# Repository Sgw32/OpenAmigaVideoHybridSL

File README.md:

# OpenAmigaVideoHybrid

!!! This version is the same, but is modified for cheaper manufacturing, only Single Sided component placement. 

OpenAmigaVideoHybrid is an Open Hardware implementation of the Video Hybrid integrated circuit used in some Commodore Amiga computers (Commodore Part No. 390229-0x).

### Summary
The *Video Hybrid*, also known as *VIDIOT*, is a hybrid integrated circuit acting as a Digital-to-Analog Converter (DAC), which converts the digital 4-bit per color video signal of the Amiga into standard (analog) signals suitable to drive a monitor or TV.

It is used in Amiga models A500, A500+, A1000, A2000 and A3000. The Amiga 3000 actually uses two Hybrids: one for the 15kHz video output from Denise and one for the 31kHz video output from Amber. Two Hybrids are also used in the [GBA1000 A1000 Clone](https://www.amigawiki.org/doku.php?id=de:models:gb_a1000).

It is also used in some add-on cards, such as the [Commodore A2320 Deinterlacer](https://amiga.resource.cx/exp/a2320).

The Video Hybrid is a reliable component that usually "just works", but if it gets damaged there is no way of repairing it, the only option is to replace it.

### Architecture
The Video Hybrid has 5 sections, one for each of the red, green and blue colors, one for the synchronization signal and one for a composite monochrome signal.

The red, green and blue sections are identical: first, the digital signals are mixed together using the typical *binary-weighted resistors* DAC configuration. After that, the level of the resulting signal is amplified through an NPN transistor. At the output, the signal is terminated at 75 ohms, as is typical for video signals.

The composite signal is generated in a similar way. The only significant differences are that the weighting resistors have different values and that the amplifier has two stages (NPN + PNP), in order to achieve a higher gain.

The synchronization signal is digital by nature, thus it needs no conversion, only some amplification.

### Components
It should now be clear that the Video Hybrid is not much more than a bunch of resistors and transistors, plus a few capacitors.

The original Video Hybrid uses a lot of resistance values which are rather odd by today's standards. While resistors with said values can still be found, they are becoming increasingly rarer and rather expensive.

Besides that, while the basic circuit has always remained the same, Commodore has used different values for some resistors in different revisions of the Video Hybrid. In particular, revision 3 uses higher resistance values in the synchronization signal section. Presumably, this was done to suppress crosstalk among the RGB channels (especially at 31kHz).

What this all means is that newer designs should use different values that are cheap and easy to find, while maintaining functionality and performance.

The tables below lists the component values originally used by Commodore, along with some alternative values readily available in the E24 series, which is common and cheap today. Another column shows the values I actually use.

|Resistors                                     |390229-01/02|390229-03|E24   |Sukko's     |Manufacturer Part Number (MPN)               |
|----------------------------------------------|------------|---------|------|------------|---------------------------------------------|
|R1, R9, R17, R25\*\*                          |1k          |1k       |1k    |1k          |CRG0805F1K0                                  |
|R2, R10, R18                                  |2k          |2k       |2k    |2k          |RMC1/10K202FTP                               |
|R3\*, R11\*, R19\*                            |4k          |4k       |3.9k  |8.2k\|\|8.2k|4.02k = CRCW08054K02FKEA, 3.9k = CRG0805F3K9 |
|R4\*, R12\*, R20\*                            |8k          |8k       |8.2k  |8.2k        |8.06k = CRCW08058K06FKEA, 8.2k = CRG0805F8K2 |
|R5, R13, R21                                  |470         |470      |470   |470         |CRG0805F470R                                 |
|R6, R14, R22                                  |390         |390      |390   |390         |CRG0805F390R                                 |
|R7, R8, R15, R16, R23, R24, R29\*\*, R39\*\*\*|75          |75       |75    |75          |ERJ6RED75R0V                                 |
|R26\*\*                                       |220         |220      |220   |220         |CRG0805F220R                                 |
|R27\*\*                                       |27k         |27k      |27k   |22k         |27k = CRG0805F27K                            |
|R28\*\*                                       |150         |150      |150   |220         |150 = CRG0805F150R                           |
|R30\*\*\*                                     |18k         |90.9k    |91k   |100k        |                                             |
|R31\*\*\*                                     |7.5k        |37.4k    |62k   |68k         |68k = CRG0805F68K                            |
|R32\*\*\*                                     |2.7k        |13.3k    |22k   |22k         |22k = RMC1/10K223FTP                         |
|R33\*\*\*                                     |1.2k        |6.04k    |10k   |22k\|\|22k  |                                             |
|R34\*\*\*                                     |7.5k        |37.4k    |62k   |68k         |                                             |
|R35\*\*\*                                     |3.9k        |19.6k    |20k   |22k         |                                             |
|R36\*\*\*                                     |120         |270      |220   |220         |                                             |
|R37\*\*\*, R38\*\*\*                          |36          |36       |36    |75\|\|75    |                                             |
|**Different Parts Count**                     |**17**      |**17**   |**16**|**10**      |                                             |

|Other Components                    |Value/MPN|
|------------------------------------|---------|
|C1, C2, C3, C4\*\*, C5\*\*\*        |100nF    |
|Q1, Q2, Q3, Q4\*\*, Q5\*\*\*        |MMBT3904 |
|Q6\*\*\*                            |MMBT3906 |

Notes:
- To achieve the highest video quality, it is strongly recommended to **use resistors with 1% tolerance** (or less) everywhere.
- *In theory*, components marked with a single asterisk* are crucial for a precise and coherent conversion of color data from digital to analog, therefore it should be recommended to stay as close as possible to the original values used by Commodore, encouraging the usage of 4.02k and 8.06k resistors (properly from the E96 series). *In practice*, my eye can't see any apparent differences when using the indicated values from the E24 series.
- Components marked with two asterisks\*\* are only used by the circuit that amplifies the synchronization signal. Normally, Amigas bring to the video connector only the raw, unamplified signal, making this circuit, and thus these components, totally useless. This is the case, for instance, on A500 Rev.5 boards, where the signal is unrouted. On A500 Rev.8A boards, the amplified and unamplified signals are brought to a jumper pad (JP11), which by default connects the unamplified signal. I'm currently not sure on what other mainboard revisions and other Amiga models do, but there's a good chance that you can get away without mounting these components at all.
- Components marked with three asterisks\*\*\* are only used by the circuit that generates the composite video signal. Since most of the original resistor values are uncommon, and since I don't think anybody really uses the composite output at all, I would just recommend not to mount these parts. If you really care for the (monochrome!) composite output, I wouldn't bother hunting down the correct parts and would just use the approximate values from the E24 series: they might produce a signal that is out-of-standard and that might blow your TV (I take no responsibility, use at your own risk!), but my tests show that they yield a decent image that can still be used for whatever a monochrome output can be useful for. Finally, note that all of these components (and only them!) have been grouped on the back side of the board for quick identification.
- Values listed in the *Sukko's* column are those that I actually use, in order to cut component costs and the number of different components. The \|\| symbol means "parallel", i.e.: just solder two resistors one over the other. These values work fine with my A500 and my TV and yield results that are satifactory for me, but they might produce a signal that is out-of-standard and that might blow your TV. Again, I take no responsibility, use at your own risk!
- The last column lists the MPN (Manufacturer Part Number) for some reasonably-priced components that I personally tested. With that number, you will be able to buy that exact model of component I used in any shop that's selling electronic components.

### Installation
Currently, OpenAmigaVideoHybrid has only been tested on the A500. On this model, you can mount it in vertical as the original Video Hybrid by using 90-degree pin headers, but I recommend a different approach:
- Remove your original Video Hybrid, taking care not to lift any traces.
- Install a row of [female *machined header pins*](https://raw.githubusercontent.com/SukkoPera/OpenAmigaVideoHybrid/master/doc/round_pin_headers_female.jpg): these will allow you to install again an original Commodore Video Hybrid, should you want to, and [it will fit snugly](https://raw.githubusercontent.com/SukkoPera/OpenAmigaVideoHybrid/master/doc/original_socketed.jpg).
- Solder a row of [male *machined header pins*](https://raw.githubusercontent.com/SukkoPera/OpenAmigaVideoHybrid/master/doc/round_pin_headers_male.jpg) to your OpenAmigaVideoHybrid: now [it will also fit just as snugly](https://raw.githubusercontent.com/SukkoPera/OpenAmigaVideoHybrid/master/doc/oavh_installed.jpg) and rest just above the output video buffer chips, without touching them and ensuring sufficient heat dissipation.

### License
OpenAmigaVideoHybrid is Open Hardware. If you make any modifications to the board, please contribute them back.

### Disclaimer
OpenAmigaVideoHybrid is provided to you ‘as is’ and without any express or implied warranties whatsoever with respect to its functionality, operability or use, including, without limitation, any implied warranties of merchantability, fitness for a particular purpose or infringement. We expressly disclaim any liability whatsoever for any direct, indirect, consequential, incidental or special damages, including, without limitation, lost revenues, lost profits, losses resulting from business interruption or loss of data, regardless of the form of action or legal theory under which the liability may be asserted, even if advised of the possibility or likelihood of such damages.

### Support the Project
Since the project is open you are free to get the PCBs made by your preferred manufacturer, however in case you want to support the development, you can order them from PCBWay through this link:

You get cheap, professionally-made and good quality PCBs, I get some credit that will help with this and [other projects](https://www.pcbway.com/project/member/shareproject/?bmbid=41100). You won't even have to worry about the various PCB options, it's all pre-configured for you!

Also, if you still have to register to that site, [you can use this link](https://www.pcbway.com/setinvite.aspx?inviteid=41100) to get some bonus initial credit (and yield me some more).

Again, if you want to use another manufacturer, feel free to, don't feel obligated :).

### Get Support
If you need help or have questions, you can join [the official Telegram group](https://t.me/joinchat/HUHdWBC9J9JnYIrvTYfZmg).

### Thanks
- The PCB layout was initially inspired by [kipper2k's Video Hybrid Replacement](http://eab.abime.net/showthread.php?t=68311).
- This page contains a lot of content translated from [amigawiki](http://www.amigawiki.de/doku.php?id=de:parts:vidiot).
- [A good tutorial on DAC architectures](http://www.circuitstoday.com/digital-to-analog-converters-da) helped me to get a better understanding of DACs.
- [This](http://logwell.com/tech/components/resistor_values.html) helped me understand the rationale behind the actual resistor values available on the market.

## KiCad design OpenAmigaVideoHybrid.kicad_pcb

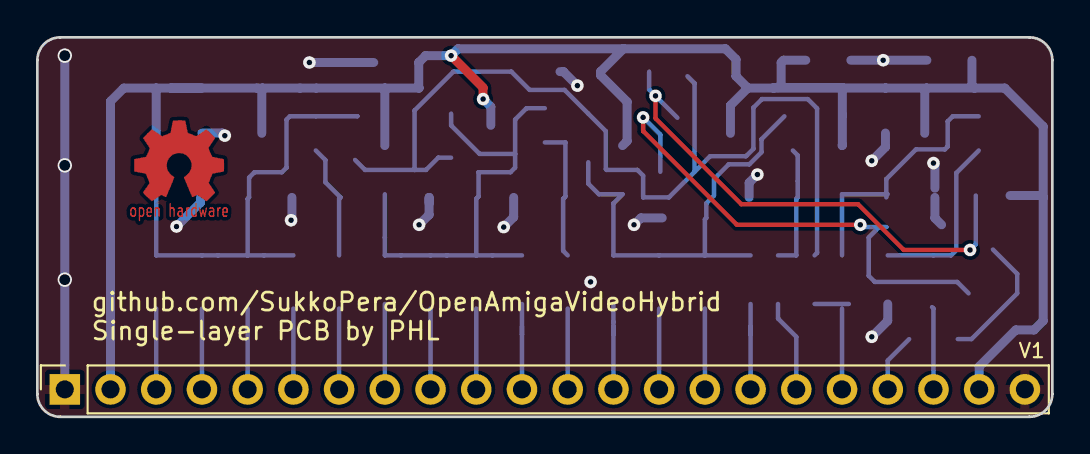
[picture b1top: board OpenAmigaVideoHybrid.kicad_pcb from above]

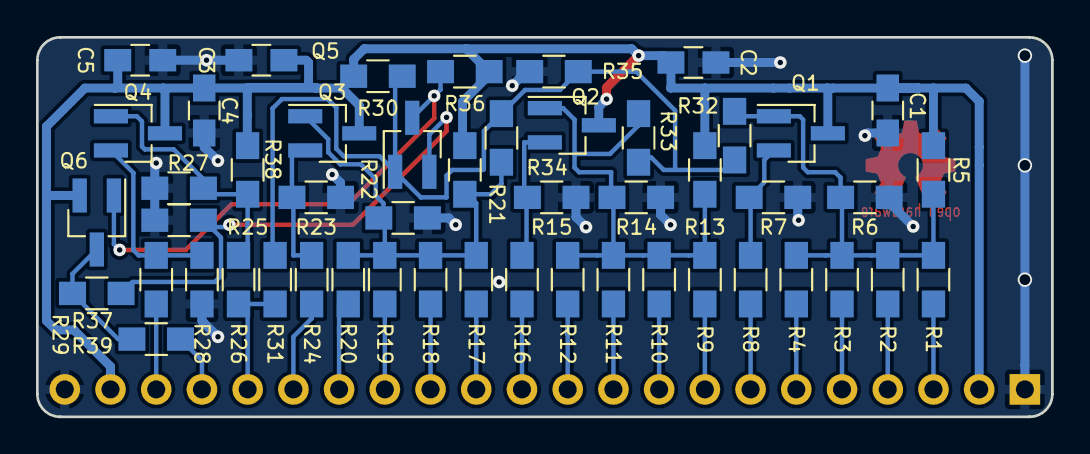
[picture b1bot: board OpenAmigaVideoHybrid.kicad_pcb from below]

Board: 2 copper layers, 56.4 x 21.1 mm, 52 parts (51 on the bottom side), 32 nets.

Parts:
C1, C2, C3, C4, C5: 100n; C_0805_HandSoldering
J1: Conn_01x22; Pin_Header_Straight_1x22_Pitch2.54mm
J99: OSHW_LOGO; Logo_copper_OSHW_6x6mm
Q1, Q2, Q3, Q4, Q5: 2N3904; 2N3904_2N3906_SOT-23
Q6: 2N3906; 2N3904_2N3906_SOT-23
R1, R9, R17, R25: 1k; R_0805_HandSoldering
R2, R10, R18: 2k; R_0805_HandSoldering
R3, R11, R19: 4k; R_0805_HandSoldering
R4, R12, R20: 8k; R_0805_HandSoldering
R5, R13, R21: 470; R_0805_HandSoldering
R6, R14, R22: 390; R_0805_HandSoldering
R7, R8, R15, R16, R23, R24, R29, R39: 75; R_0805_HandSoldering
R26, R36: 220; R_0805_HandSoldering
R27: 27k; R_0805_HandSoldering
R28: 150; R_0805_HandSoldering
R30: 90.9k; R_0805_HandSoldering
R31, R34: 37.4k; R_0805_HandSoldering
R32: 13.3k; R_0805_HandSoldering
R33: 6.04k; R_0805_HandSoldering
R35: 19.6k; R_0805_HandSoldering
R37, R38: 36; R_0805_HandSoldering

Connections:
/blue: J1.17, R24.1
/comp: J1.19, R39.1
/csync: J1.18, R26.2, R31.2
/db0: J1.16, R20.2
/db1: J1.15, R19.2
/db2: J1.14, R18.2
/db3: J1.13, R17.2
/dg0: J1.11, R12.2
/dg1: J1.10, R11.2
/dg2: J1.9, R10.2
/dg3: J1.8, R9.2
/dr0: J1.6, R4.2
/dr1: J1.5, R3.2
/dr2: J1.4, R2.2
/dr3: J1.3, R1.2
/green: J1.12, R16.1
/red: J1.7, R8.1
/sync: J1.20, R29.1
GND: C1.2, C2.2, C3.2, C4.2, C5.2, J1.1, J1.22, R6.2, R7.2, R14.2, R15.2, R22.2, R23.2, R27.2, R28.2, R35.2, R38.2
unnamed: Q1.1, R7.1, R8.2
unnamed: Q1.2, R1.1, R2.1, R3.1, R4.1, R5.2, R6.1, R32.2
unnamed: Q2.1, R15.1, R16.2
unnamed: Q2.2, R9.1, R10.1, R11.1, R12.1, R13.2, R14.1, R33.2
unnamed: Q3.1, R23.1, R24.2
unnamed: Q3.2, R17.1, R18.1, R19.1, R20.1, R21.2, R22.1, R34.2
unnamed: Q4.1, R28.1, R29.2
unnamed: Q4.2, R25.2, R26.1, R27.1
unnamed: Q5.1, R37.2, R38.1
unnamed: Q5.2, R30.2, R31.1, R32.1, R33.1, R34.1, R35.1
unnamed: Q5.3, Q6.2, R36.2
unnamed: Q6.3, R37.1, R39.2
VCC: C1.1, C2.1, C3.1, C4.1, C5.1, J1.2, J1.21, Q1.3, Q2.3, Q3.3, Q4.3, Q6.1, R5.1, R13.1, R21.1, R25.1, R30.1, R36.1

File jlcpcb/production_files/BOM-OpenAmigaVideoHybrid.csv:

Comment,Designator,Footprint,LCSC
100n,C1,C_0805_HandSoldering,
100n,C2,C_0805_HandSoldering,
100n,C3,C_0805_HandSoldering,
100n,C4,C_0805_HandSoldering,
100n,C5,C_0805_HandSoldering,
1k,R1,R_0805_HandSoldering,
2k,R2,R_0805_HandSoldering,
4k,R3,R_0805_HandSoldering,
8k,R4,R_0805_HandSoldering,
470,R5,R_0805_HandSoldering,
390,R6,R_0805_HandSoldering,
75,R7,R_0805_HandSoldering,
75,R8,R_0805_HandSoldering,
1k,R9,R_0805_HandSoldering,
2k,R10,R_0805_HandSoldering,
4k,R11,R_0805_HandSoldering,
8k,R12,R_0805_HandSoldering,
470,R13,R_0805_HandSoldering,
390,R14,R_0805_HandSoldering,
75,R15,R_0805_HandSoldering,
75,R16,R_0805_HandSoldering,
1k,R17,R_0805_HandSoldering,
2k,R18,R_0805_HandSoldering,
4k,R19,R_0805_HandSoldering,
8k,R20,R_0805_HandSoldering,
470,R21,R_0805_HandSoldering,
390,R22,R_0805_HandSoldering,
75,R23,R_0805_HandSoldering,
75,R24,R_0805_HandSoldering,
1k,R25,R_0805_HandSoldering,
220,R26,R_0805_HandSoldering,
27k,R27,R_0805_HandSoldering,
150,R28,R_0805_HandSoldering,
75,R29,R_0805_HandSoldering,
90.9k,R30,R_0805_HandSoldering,
37.4k,R31,R_0805_HandSoldering,
13.3k,R32,R_0805_HandSoldering,
6.04k,R33,R_0805_HandSoldering,
37.4k,R34,R_0805_HandSoldering,
19.6k,R35,R_0805_HandSoldering,
220,R36,R_0805_HandSoldering,
36,R37,R_0805_HandSoldering,
36,R38,R_0805_HandSoldering,
75,R39,R_0805_HandSoldering,
2N3904,Q1,2N3904_2N3906_SOT-23,
2N3904,Q2,2N3904_2N3906_SOT-23,
2N3904,Q3,2N3904_2N3906_SOT-23,
2N3904,Q4,2N3904_2N3906_SOT-23,
2N3904,Q5,2N3904_2N3906_SOT-23,
2N3906,Q6,2N3904_2N3906_SOT-23,
Conn_01x22,J1,Pin_Header_Straight_1x22_Pitch2.54mm,

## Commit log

2025-02-13 Modify PCB and add production files
2025-02-13 Modify README
